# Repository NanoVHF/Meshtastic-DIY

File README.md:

# Meshtastic-DIY

Dear friends. If you have just learned what a Meshtastic-radio network is, if you are interested in the topic, if you already have a radio modem, and you would like to breathe life into it, then …
I have written a large series of 4 articles for the Russian-speaking community. This is more than the usual FAQ. This is a complete guide to action.
At the moment, the articles are written in Russian for a Russian-speaking audience. You can easily translate the article in your google chrome browser into your national language. Perhaps the Google translation will be slightly incorrect, with inaccuracies or errors.
Also, I am considering translating the article into real technical English.

PART 1 : https://habr.com/ru/post/568394/
The article is devoted to the general principles of the Meshtastic-network.

PART 2 : https://habr.com/ru/post/568526/
The article is devoted to branded radio modems with aliexpress stores.

PART 3 : https://habr.com/ru/post/568534/
The article is devoted to the radio amateur design and self-assembly of the radio modem (DIY).

PART 4 : https://habr.com/ru/post/569788/
A detailed step-by-step guide to flashing a radio modem and setting up a local radio network.

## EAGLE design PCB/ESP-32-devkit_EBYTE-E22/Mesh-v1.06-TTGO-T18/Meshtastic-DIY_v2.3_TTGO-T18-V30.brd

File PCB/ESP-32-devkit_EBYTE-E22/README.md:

# PCB

Based on [DIY v.1 shematics](https://github.com/NanoVHF/Meshtastic-DIY/tree/main/Schematics/E-Byte_E22) for using with `ESP32 WROOM-32 DevKit 38 pins` and `EBYTE E22-XXXM30S/E22-XXXM22S` modules.

Design by Denis Gorbunov (https://t.me/deaxx)

## Mesh-v1.01-2LCD-FreePins - Basic
- ESP32 WROOM-32 DevKit 38 pins,
- LORA: EBYTE E22-XXXM30S/E22-XXXM22S (selectable module). LoRa is connected via [an additional adapter board](#ebyte-e22-xxxmxxs-adapter-board),
- GPS,
- LCD (select different screens via jumpers: Vcc/GND or GND/Vcc),
- FR (free pins) - free ESP32 pins are placed along the edges of the board.

## Mesh-v1.02-2LCD - Narrow for placing inside a pipe
- ESP32 WROOM-32 DevKit 38 pins,
- LORA: EBYTE E22-XXXM30S/E22-XXXM22S (selectable module. LoRa module soldered directly to the board,
- GPS,
- LCD (select different screens via jumpers: Vcc/GND or GND/Vcc).

## Mesh-v1.02-2LCD-FreePins - Narrow for placing inside a pipe
- ESP32 WROOM-32 DevKit 38 pins,
- LORA: EBYTE E22-XXXM30S/E22-XXXM22S (selectable module. LoRa module soldered directly to the board,
- GPS,
- LCD (select different screens via jumpers: Vcc/GND or GND/Vcc),
- FR (free pins) - free ESP32 pins are placed along the edges of the board.

## Mesh-v1.03-2LCD-FreePins - Compact wearable
- ESP32 WROOM-32 DevKit 38 pins,
- LORA: EBYTE E22-XXXM30S/E22-XXXM22S (selectable module). LoRa is connected via [an additional adapter board](#ebyte-e22-xxxmxxs-adapter-board),
- GPS,
- LCD (select different screens via jumpers: Vcc/GND or GND/Vcc),
- FR (free pins) - free ESP32 pins are placed along the edges of the board.

## Mesh-v1.04-TTGO-T8 - Compact wearable @ WROOWER T8 Lilygo
- ESP32 *WROOWER T8 Lilygo* 38 pins,
- LORA: EBYTE E22-XXXM30S/E22-XXXM22S (selectable module). LoRa is connected via [an additional adapter board](#ebyte-e22-xxxmxxs-adapter-board),
- GPS,
- LCD (select different screens via jumpers: Vcc/GND or GND/Vcc),
- FR (free pins) - free ESP32 pins are placed along the edges of the board.

## Meshtastic-DIY_v1.05 - Square one
- ESP32 WROOM-32 DevKit 38 pins,
- LORA: EBYTE E22-XXXM30S/E22-XXXM22S (selectable module),
- GPS,
- LCD (select different screens via jumpers: Vcc/GND or GND/Vcc),
- Optional active buzzer.

## Meshtastic-DIY_v1.06 - TTGO T-Energy T18 V3.0 HAT
- *Lilygo TTGO T-Energy T18 V3.0*,
- LORA: EBYTE E22-XXXM30S/E22-XXXM22S (selectable module),
- LCD (select different screens via jumpers: Vcc/GND or GND/Vcc).

## EBYTE E22-xxxMxxS adapter board

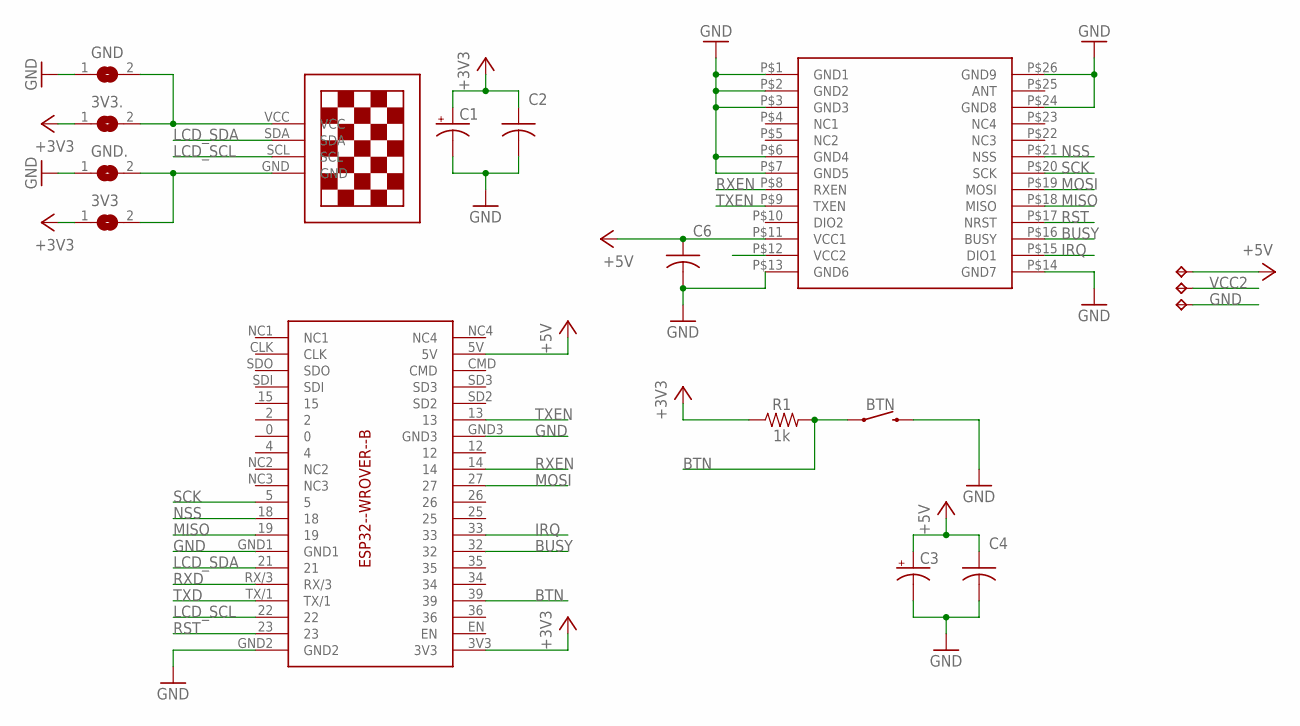
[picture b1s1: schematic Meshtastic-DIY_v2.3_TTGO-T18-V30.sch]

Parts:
3V3, 3V3.: SJ
BTN: MOMENTARY-SWITCH-SPST-SMD-5.2MM; TACTILE_SWITCH_SMD_5.2MM
C1, C3: 100uF; EIA7343
C2, C4, C6: 100nF; C025-024X044
GND, GND.: SJ
R1: 1k; AXIAL-0.1
TP1, TP2, TP3: TPTP14SQ; TP14SQ
U$1: 13"OLED13"OLED; 1.3"OLED
U$2: E22-XXXMXXS
U$4: TTGO-T18_V3

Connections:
+3V3: 3V3.1, 3V3..1, C1.A (+), C2.1, R1.P$1 (1), U$4.3V3
+5V: C3.A (+), C4.1, C6.1, TP1.TP, U$2.P$11 (VCC1), U$4.5V
BTN: BTN.1, R1.P$2 (2), U$4.39
BUSY: U$2.P$16 (BUSY), U$4.32
GND: BTN.3 (2), C1.C (-), C2.2, C3.C (-), C4.2, C6.2, GND.1, GND..1, TP3.TP, U$2.P$1 (GND1), U$2.P$2 (GND2), U$2.P$3 (GND3), U$2.P$6 (GND4), U$2.P$7 (GND5), U$2.P$13 (GND6), U$2.P$14 (GND7), U$2.P$24 (GND8), U$2.P$26 (GND9), U$4.GND1, U$4.GND2, U$4.GND3
IRQ: U$2.P$15 (DIO1), U$4.33
LCD_SCL: U$1.SCL, U$4.22
LCD_SDA: U$1.SDA, U$4.21
MISO: U$2.P$18 (MISO), U$4.19
MOSI: U$2.P$19 (MOSI), U$4.27
unnamed: 3V3.2, GND..2, U$1.GND
unnamed: 3V3..2, GND.2, U$1.VCC
NSS: U$2.P$21 (NSS), U$4.18
RST: U$2.P$17 (NRST), U$4.23
RXD: U$4.RX/3
RXEN: U$2.P$8 (RXEN), U$4.14
SCK: U$2.P$20 (SCK), U$4.5
TXD: U$4.TX/1
TXEN: U$2.P$9 (TXEN), U$4.13
VCC2: TP2.TP, U$2.P$12 (VCC2)

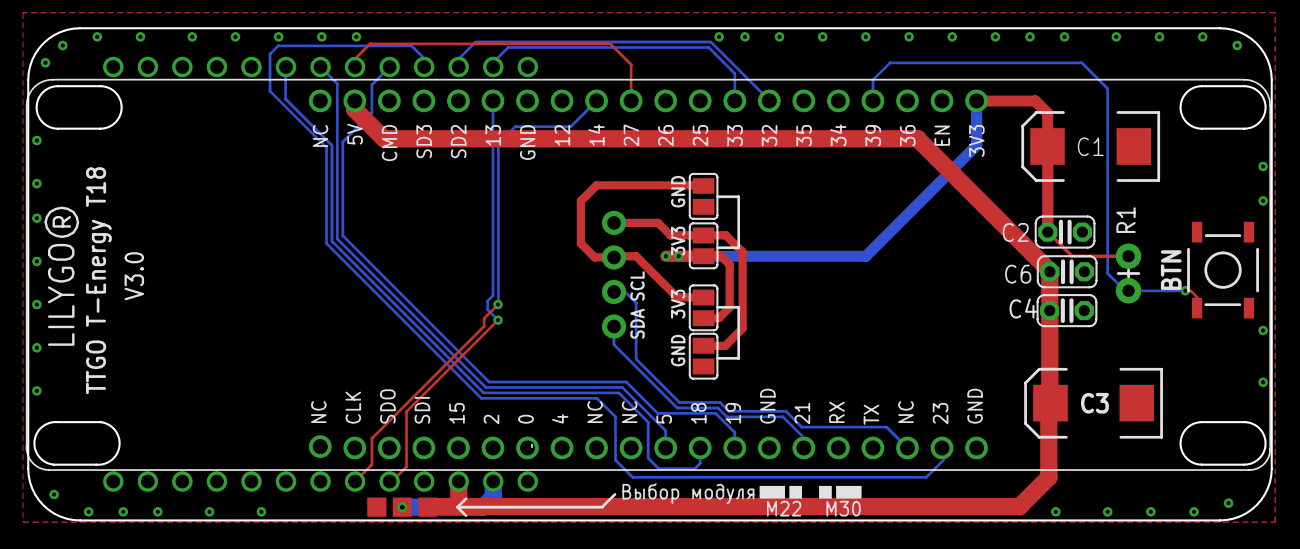
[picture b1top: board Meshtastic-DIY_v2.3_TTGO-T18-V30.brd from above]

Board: 2 copper layers, 91.4 x 36.2 mm, 17 parts (1 on the bottom side), 18 nets.

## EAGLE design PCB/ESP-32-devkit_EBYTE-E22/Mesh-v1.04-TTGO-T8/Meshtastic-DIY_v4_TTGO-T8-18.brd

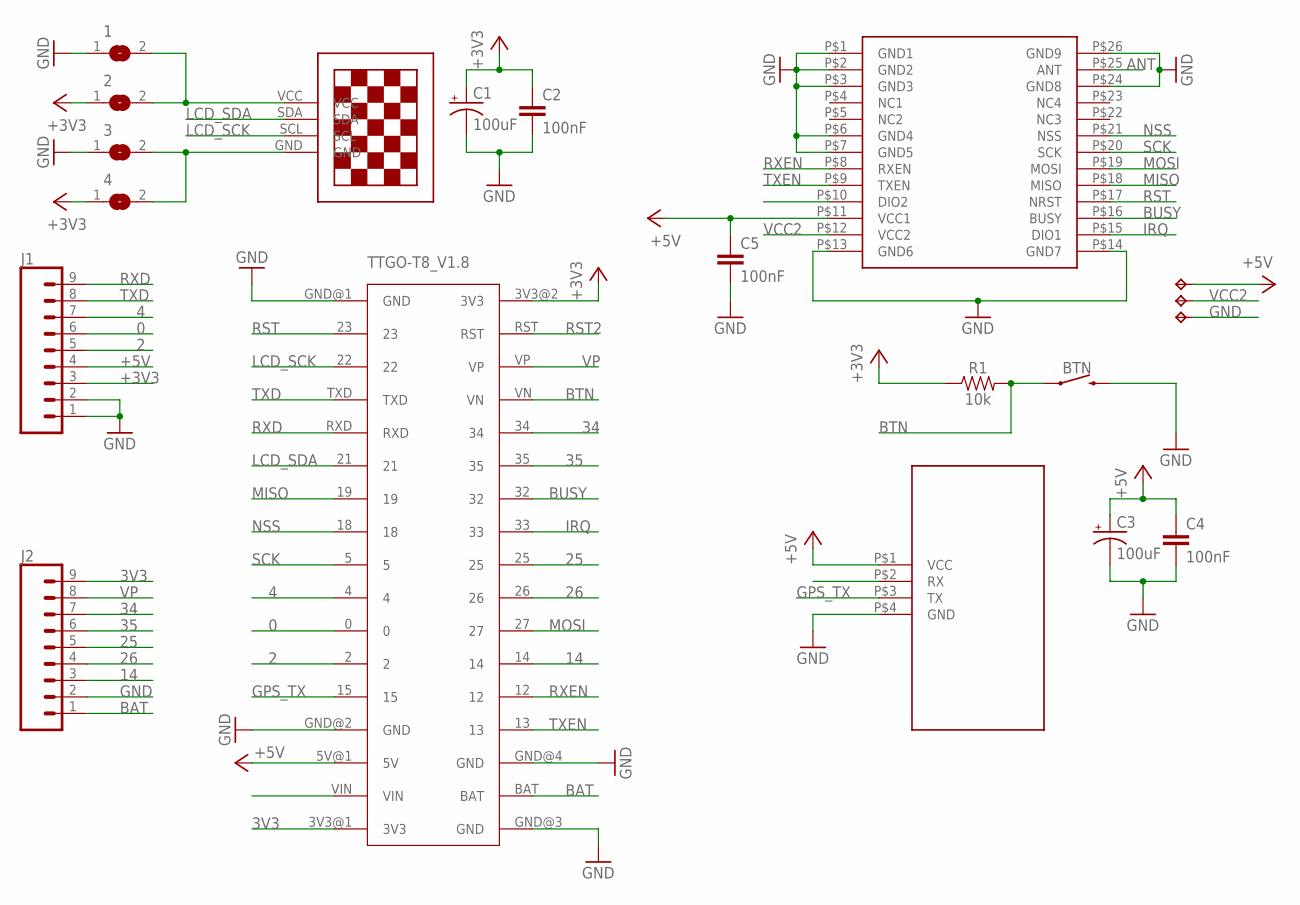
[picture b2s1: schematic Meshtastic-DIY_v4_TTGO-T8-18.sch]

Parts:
1, 2, 3, 4: SJ
BTN: MOMENTARY-SWITCH-SPST-SMD-5.2MM; TACTILE_SWITCH_SMD_5.2MM
C1, C3: 100uF; EIA7343
C2, C4, C5: 100nF; 0805
J1, J2: CONN_09NO_SILK; 1X09_NO_SILK
R1: 10k; 1210
TP1, TP2, TP3: TPTP14SQ; TP14SQ
TTGO-T8_V1.8: TTGO-T8_V18
U$1: 13"OLED13"OLED; 1.3"OLED
U$2: E22-XXXMXXS
U$3: GPS-NEO

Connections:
0: J1.6, TTGO-T8_V1.8.0
2: J1.5, TTGO-T8_V1.8.2
3V3: J2.9, TTGO-T8_V1.8.3V3@1 (3V3)
4: J1.7, TTGO-T8_V1.8.4
14: J2.3, TTGO-T8_V1.8.14
25: J2.5, TTGO-T8_V1.8.25
26: J2.4, TTGO-T8_V1.8.26
34: J2.7, TTGO-T8_V1.8.34
35: J2.6, TTGO-T8_V1.8.35
+3V3: 2.1, 4.1, C1.A (+), C2.1, J1.3, R1.1, TTGO-T8_V1.8.3V3@2 (3V3)
+5V: C3.A (+), C4.1, C5.1, J1.4, TP1.TP, TTGO-T8_V1.8.5V@1 (5V), U$2.P$11 (VCC1), U$3.P$1 (VCC)
ANT: U$2.P$25 (ANT)
BAT: J2.1, TTGO-T8_V1.8.BAT
BTN: BTN.1, R1.2, TTGO-T8_V1.8.VN
BUSY: TTGO-T8_V1.8.32, U$2.P$16 (BUSY)
GND: 1.1, 3.1, BTN.3 (2), C1.C (-), C2.2, C3.C (-), C4.2, C5.2, J1.1, J1.2, J2.2, TP3.TP, TTGO-T8_V1.8.GND@1 (GND), TTGO-T8_V1.8.GND@2 (GND), TTGO-T8_V1.8.GND@3 (GND), TTGO-T8_V1.8.GND@4 (GND), U$2.P$1 (GND1), U$2.P$2 (GND2), U$2.P$3 (GND3), U$2.P$6 (GND4), U$2.P$7 (GND5), U$2.P$13 (GND6), U$2.P$14 (GND7), U$2.P$24 (GND8), U$2.P$26 (GND9), U$3.P$4 (GND)
GPS_TX: TTGO-T8_V1.8.15, U$3.P$3 (TX)
IRQ: TTGO-T8_V1.8.33, U$2.P$15 (DIO1)
LCD_SCK: TTGO-T8_V1.8.22, U$1.SCL
LCD_SDA: TTGO-T8_V1.8.21, U$1.SDA
MISO: TTGO-T8_V1.8.19, U$2.P$18 (MISO)
MOSI: TTGO-T8_V1.8.27, U$2.P$19 (MOSI)
unnamed: 3.2, 4.2, U$1.GND
unnamed: 1.2, 2.2, U$1.VCC
NSS: TTGO-T8_V1.8.18, U$2.P$21 (NSS)
RST: TTGO-T8_V1.8.23, U$2.P$17 (NRST)
RST2: TTGO-T8_V1.8.RST
RXD: J1.9, TTGO-T8_V1.8.RXD
RXEN: TTGO-T8_V1.8.12, U$2.P$8 (RXEN)
SCK: TTGO-T8_V1.8.5, U$2.P$20 (SCK)
TXD: J1.8, TTGO-T8_V1.8.TXD
TXEN: TTGO-T8_V1.8.13, U$2.P$9 (TXEN)
VCC2: TP2.TP, U$2.P$12 (VCC2)
VP: J2.8, TTGO-T8_V1.8.VP

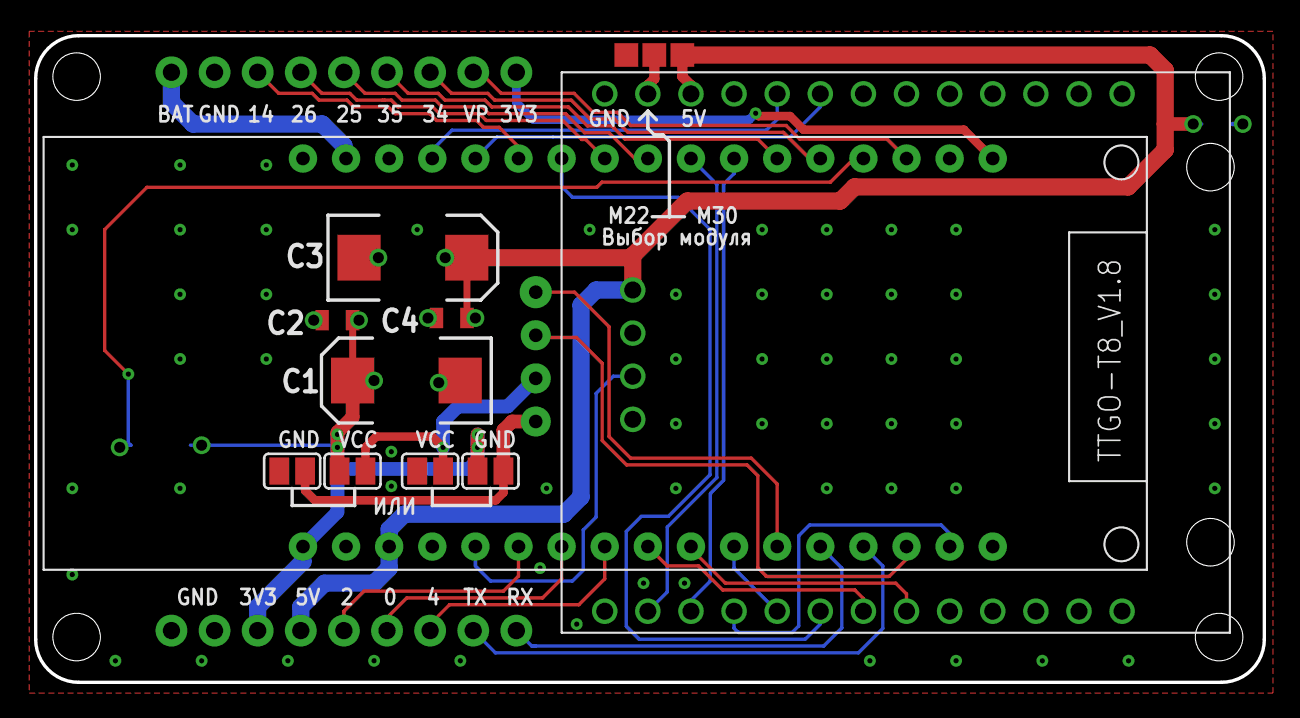
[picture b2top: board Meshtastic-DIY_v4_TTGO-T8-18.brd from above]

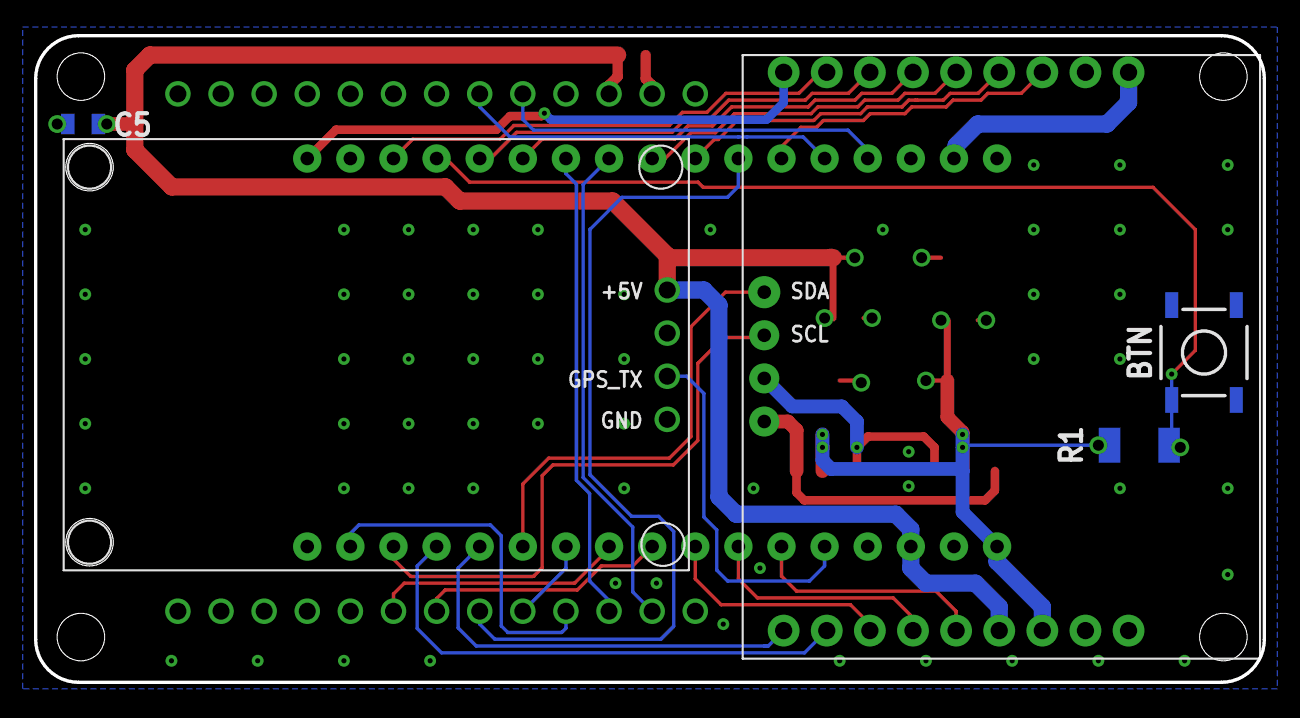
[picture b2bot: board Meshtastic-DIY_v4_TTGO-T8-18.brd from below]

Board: 2 copper layers, 72.4 x 38.1 mm, 20 parts (5 on the bottom side), 32 nets.

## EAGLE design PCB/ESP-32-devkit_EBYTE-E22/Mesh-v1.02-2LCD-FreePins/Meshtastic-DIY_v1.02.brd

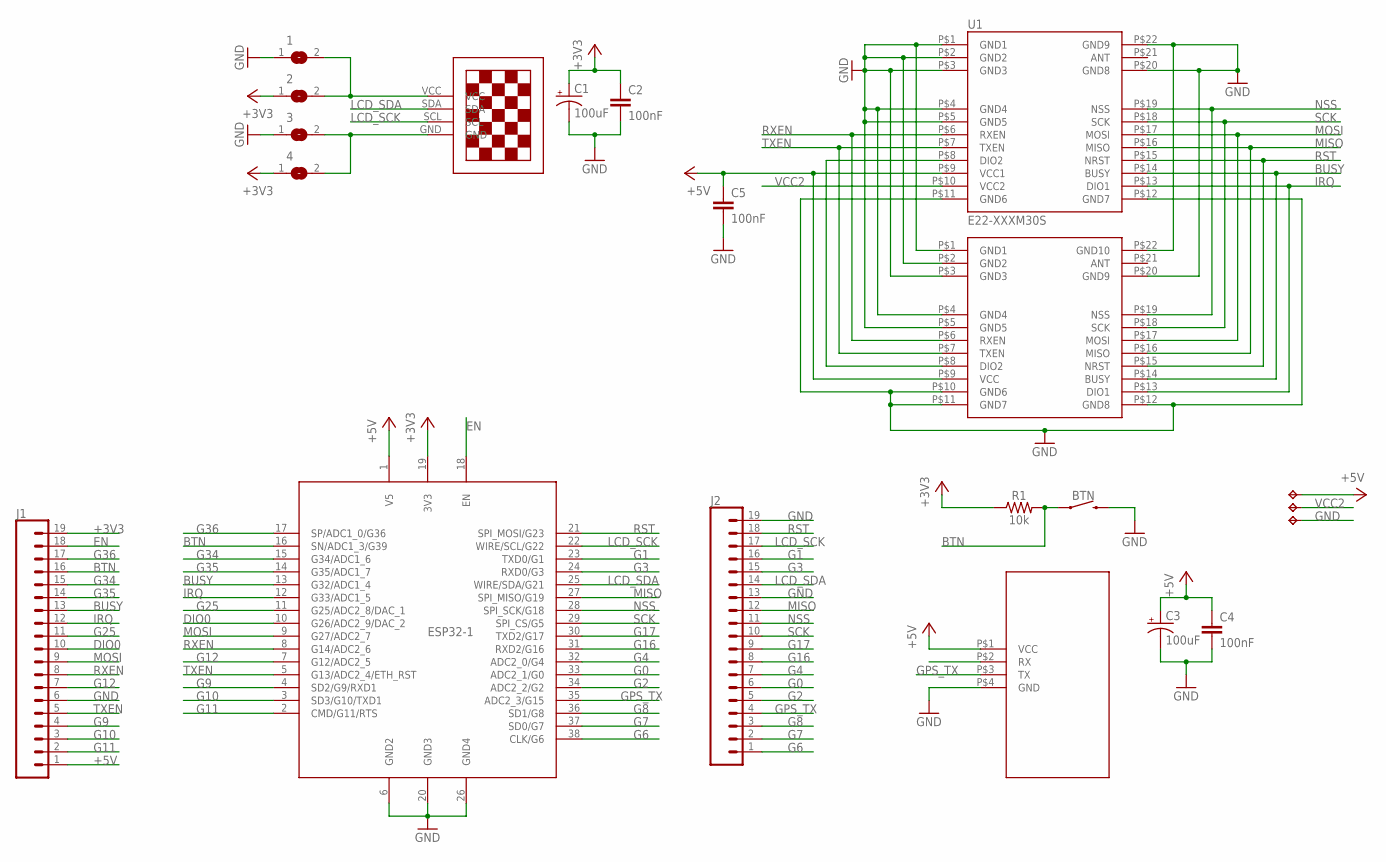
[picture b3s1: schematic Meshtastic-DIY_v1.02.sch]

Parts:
1, 2, 3, 4: SJ
BTN: MOMENTARY-SWITCH-SPST-PTH-6.0MM; TACTILE_SWITCH_PTH_6.0MM
C1, C3: 100uF; EIA7343
C2, C4, C5: 100nF; 0805
ESP32-1: NODEMCU_ESP32_WROOM_32; NODEMCU_ESP32_WROOM_32--38PINS
J1, J2: CONN_191X19_NO_SILK; 1X19_NO_SILK
R1: 10k; 1210
TP1, TP2, TP3: TPTP14SQ; TP14SQ
U1: E22-XXXM30S
U$1: 13"OLED13"OLED; 1.3"OLED
U$2: E22-XXXM22S
U$3: GPS-NEO

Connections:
+3V3: 2.1, 4.1, C1.A (+), C2.1, ESP32-1.19 (3V3), J1.19, R1.1
+5V: C3.A (+), C4.1, C5.1, ESP32-1.1 (V5), J1.1, TP1.TP, U1.P$9 (VCC1), U$2.P$9 (VCC), U$3.P$1 (VCC)
BTN: BTN.1, ESP32-1.16 (SN/ADC1_3/G39), J1.16, R1.2
BUSY: ESP32-1.13 (G32/ADC1_4), J1.13, U1.P$14 (BUSY), U$2.P$14 (BUSY)
DIO0: ESP32-1.10 (G26/ADC2_9/DAC_2), J1.10
EN: ESP32-1.18 (EN), J1.18
G0: ESP32-1.33 (ADC2_1/G0), J2.6
G1: ESP32-1.23 (TXD0/G1), J2.16
G2: ESP32-1.34 (ADC2_2/G2), J2.5
G3: ESP32-1.24 (RXD0/G3), J2.15
G4: ESP32-1.32 (ADC2_0/G4), J2.7
G6: ESP32-1.38 (CLK/G6), J2.1
G7: ESP32-1.37 (SD0/G7), J2.2
G8: ESP32-1.36 (SD1/G8), J2.3
G9: ESP32-1.4 (SD2/G9/RXD1), J1.4
G10: ESP32-1.3 (SD3/G10/TXD1), J1.3
G11: ESP32-1.2 (CMD/G11/RTS), J1.2
G12: ESP32-1.7 (G12/ADC2_5), J1.7
G16: ESP32-1.31 (RXD2/G16), J2.8
G17: ESP32-1.30 (TXD2/G17), J2.9
G25: ESP32-1.11 (G25/ADC2_8/DAC_1), J1.11
G34: ESP32-1.15 (G34/ADC1_6), J1.15
G35: ESP32-1.14 (G35/ADC1_7), J1.14
G36: ESP32-1.17 (SP/ADC1_0/G36), J1.17
GND: 1.1, 3.1, BTN.3 (2), C1.C (-), C2.2, C3.C (-), C4.2, C5.2, ESP32-1.6 (GND2), ESP32-1.20 (GND3), ESP32-1.26 (GND4), J1.6, J2.13, J2.19, TP3.TP, U1.P$1 (GND1), U1.P$2 (GND2), U1.P$3 (GND3), U1.P$4 (GND4), U1.P$5 (GND5), U1.P$11 (GND6), U1.P$12 (GND7), U1.P$20 (GND8), U1.P$22 (GND9), U$2.P$1 (GND1), U$2.P$2 (GND2), U$2.P$3 (GND3), U$2.P$4 (GND4), U$2.P$5 (GND5), U$2.P$10 (GND6), U$2.P$11 (GND7), U$2.P$12 (GND8), U$2.P$20 (GND9), U$2.P$22 (GND10), U$3.P$4 (GND)
GPS_TX: ESP32-1.35 (ADC2_3/G15), J2.4, U$3.P$3 (TX)
IRQ: ESP32-1.12 (G33/ADC1_5), J1.12, U1.P$13 (DIO1), U$2.P$13 (DIO1)
LCD_SCK: ESP32-1.22 (WIRE/SCL/G22), J2.17, U$1.SCL
LCD_SDA: ESP32-1.25 (WIRE/SDA/G21), J2.14, U$1.SDA
MISO: ESP32-1.27 (SPI_MISO/G19), J2.12, U1.P$16 (MISO), U$2.P$16 (MISO)
MOSI: ESP32-1.9 (G27/ADC2_7), J1.9, U1.P$17 (MOSI), U$2.P$17 (MOSI)
unnamed: 3.2, 4.2, U$1.GND
unnamed: 1.2, 2.2, U$1.VCC
unnamed: U1.P$8 (DIO2), U$2.P$8 (DIO2)
NSS: ESP32-1.28 (SPI_SCK/G18), J2.11, U1.P$19 (NSS), U$2.P$19 (NSS)
RST: ESP32-1.21 (SPI_MOSI/G23), J2.18, U1.P$15 (NRST), U$2.P$15 (NRST)
RXEN: ESP32-1.8 (G14/ADC2_6), J1.8, U1.P$6 (RXEN), U$2.P$6 (RXEN)
SCK: ESP32-1.29 (SPI_CS/G5), J2.10, U1.P$18 (SCK), U$2.P$18 (SCK)
TXEN: ESP32-1.5 (G13/ADC2_4/ETH_RST), J1.5, U1.P$7 (TXEN), U$2.P$7 (TXEN)
VCC2: TP2.TP, U1.P$10 (VCC2)

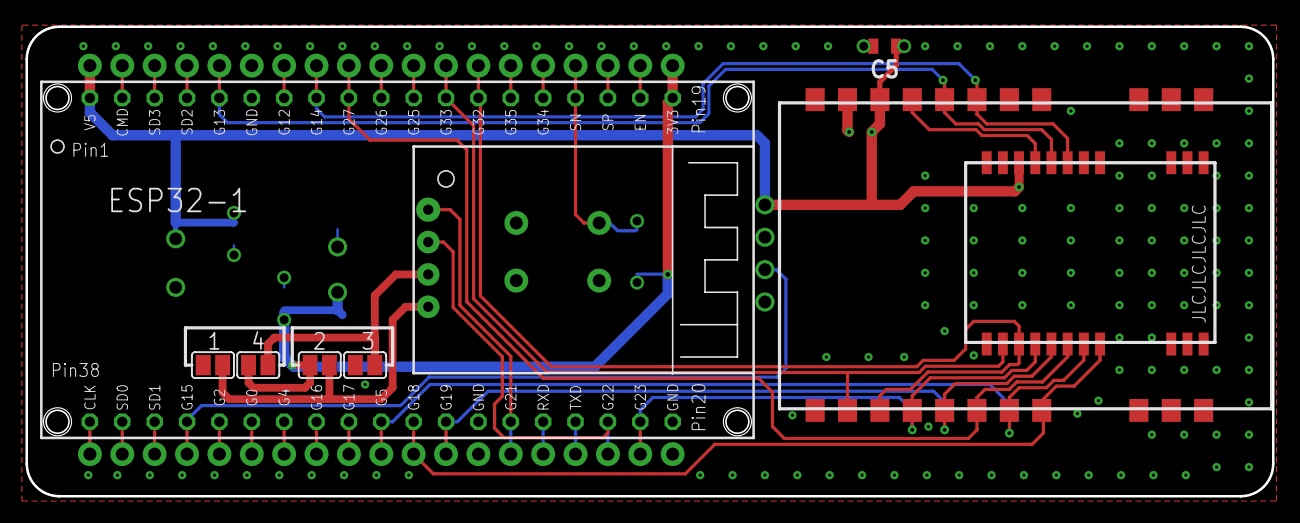
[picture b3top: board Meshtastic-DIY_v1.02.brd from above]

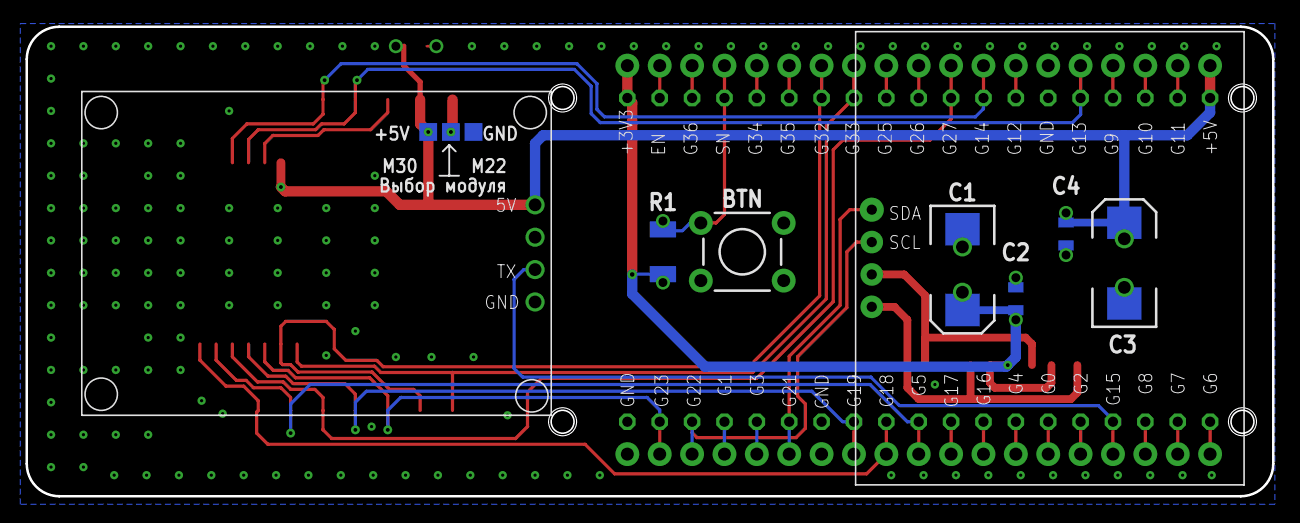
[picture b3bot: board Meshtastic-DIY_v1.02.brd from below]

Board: 2 copper layers, 97.8 x 36.8 mm, 21 parts (11 on the bottom side), 40 nets.

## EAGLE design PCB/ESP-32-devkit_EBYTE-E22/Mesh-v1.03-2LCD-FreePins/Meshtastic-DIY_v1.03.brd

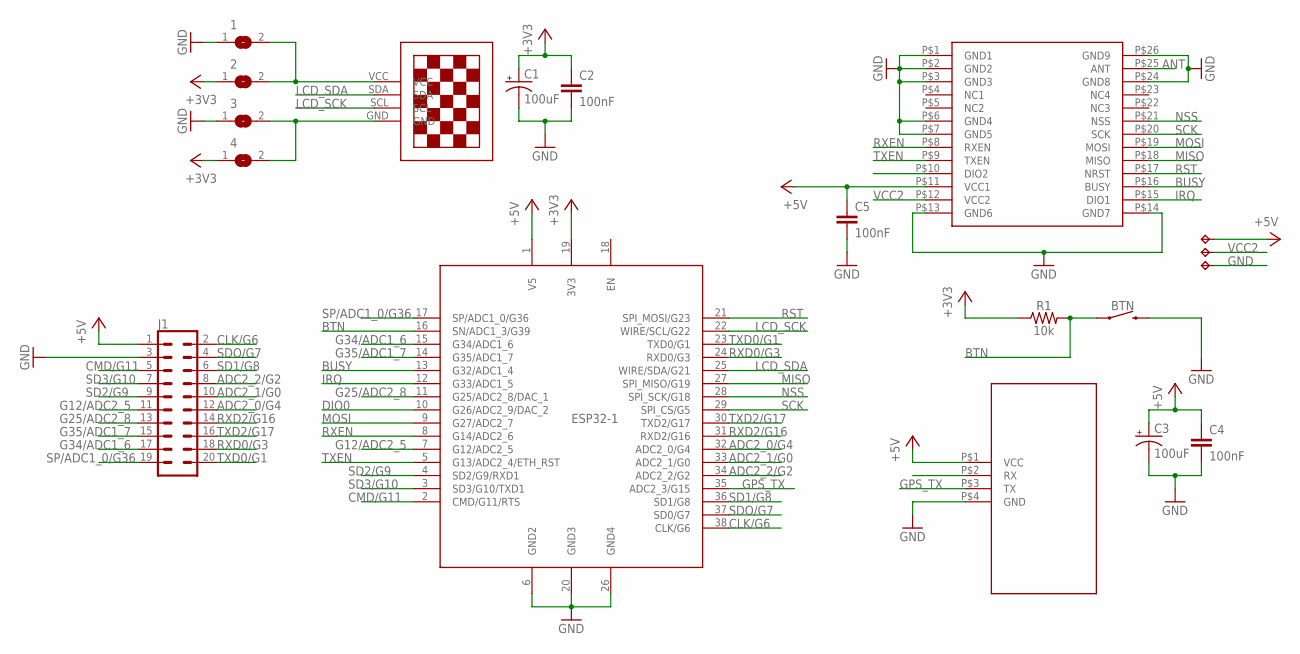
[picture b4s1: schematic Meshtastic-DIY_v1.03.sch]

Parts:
1, 2, 3, 4: SJ
BTN: MOMENTARY-SWITCH-SPST-SMD-5.2MM; TACTILE_SWITCH_SMD_5.2MM
C1, C3: 100uF; EIA7343
C2, C4, C5: 100nF; 0805
ESP32-1: NODEMCU_ESP32_WROOM_32; NODEMCU_ESP32_WROOM_32--38PINS
J1: CONN_10X2NOSILK; 2X10_NOSILK
R1: 10k; 1210
TP1, TP2, TP3: TPTP14SQ; TP14SQ
U$1: 13"OLED13"OLED; 1.3"OLED
U$2: E22-XXXMXXS
U$3: GPS-NEO

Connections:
+3V3: 2.1, 4.1, C1.A (+), C2.1, ESP32-1.19 (3V3), R1.1
+5V: C3.A (+), C4.1, C5.1, ESP32-1.1 (V5), J1.1, TP1.TP, U$2.P$11 (VCC1), U$3.P$1 (VCC)
ADC2_0/G4: ESP32-1.32 (ADC2_0/G4), J1.12
ADC2_1/G0: ESP32-1.33 (ADC2_1/G0), J1.10
ADC2_2/G2: ESP32-1.34 (ADC2_2/G2), J1.8
ANT: U$2.P$25 (ANT)
BTN: BTN.1, ESP32-1.16 (SN/ADC1_3/G39), R1.2
BUSY: ESP32-1.13 (G32/ADC1_4), U$2.P$16 (BUSY)
CLK/G6: ESP32-1.38 (CLK/G6), J1.2
CMD/G11: ESP32-1.2 (CMD/G11/RTS), J1.5
DIO0: ESP32-1.10 (G26/ADC2_9/DAC_2)
G12/ADC2_5: ESP32-1.7 (G12/ADC2_5), J1.11
G25/ADC2_8: ESP32-1.11 (G25/ADC2_8/DAC_1), J1.13
G34/ADC1_6: ESP32-1.15 (G34/ADC1_6), J1.17
G35/ADC1_7: ESP32-1.14 (G35/ADC1_7), J1.15
GND: 1.1, 3.1, BTN.3 (2), C1.C (-), C2.2, C3.C (-), C4.2, C5.2, ESP32-1.6 (GND2), ESP32-1.20 (GND3), ESP32-1.26 (GND4), J1.3, TP3.TP, U$2.P$1 (GND1), U$2.P$2 (GND2), U$2.P$3 (GND3), U$2.P$6 (GND4), U$2.P$7 (GND5), U$2.P$13 (GND6), U$2.P$14 (GND7), U$2.P$24 (GND8), U$2.P$26 (GND9), U$3.P$4 (GND)
GPS_TX: ESP32-1.35 (ADC2_3/G15), U$3.P$3 (TX)
IRQ: ESP32-1.12 (G33/ADC1_5), U$2.P$15 (DIO1)
LCD_SCK: ESP32-1.22 (WIRE/SCL/G22), U$1.SCL
LCD_SDA: ESP32-1.25 (WIRE/SDA/G21), U$1.SDA
MISO: ESP32-1.27 (SPI_MISO/G19), U$2.P$18 (MISO)
MOSI: ESP32-1.9 (G27/ADC2_7), U$2.P$19 (MOSI)
unnamed: 3.2, 4.2, U$1.GND
unnamed: 1.2, 2.2, U$1.VCC
NSS: ESP32-1.28 (SPI_SCK/G18), U$2.P$21 (NSS)
RST: ESP32-1.21 (SPI_MOSI/G23), U$2.P$17 (NRST)
RXD0/G3: ESP32-1.24 (RXD0/G3), J1.18
RXD2/G16: ESP32-1.31 (RXD2/G16), J1.14
RXEN: ESP32-1.8 (G14/ADC2_6), U$2.P$8 (RXEN)
SCK: ESP32-1.29 (SPI_CS/G5), U$2.P$20 (SCK)
SD1/G8: ESP32-1.36 (SD1/G8), J1.6
SD2/G9: ESP32-1.4 (SD2/G9/RXD1), J1.9
SD3/G10: ESP32-1.3 (SD3/G10/TXD1), J1.7
SDO/G7: ESP32-1.37 (SD0/G7), J1.4
SP/ADC1_0/G36: ESP32-1.17 (SP/ADC1_0/G36), J1.19
TXD0/G1: ESP32-1.23 (TXD0/G1), J1.20
TXD2/G17: ESP32-1.30 (TXD2/G17), J1.16
TXEN: ESP32-1.5 (G13/ADC2_4/ETH_RST), U$2.P$9 (TXEN)
VCC2: TP2.TP, U$2.P$12 (VCC2)

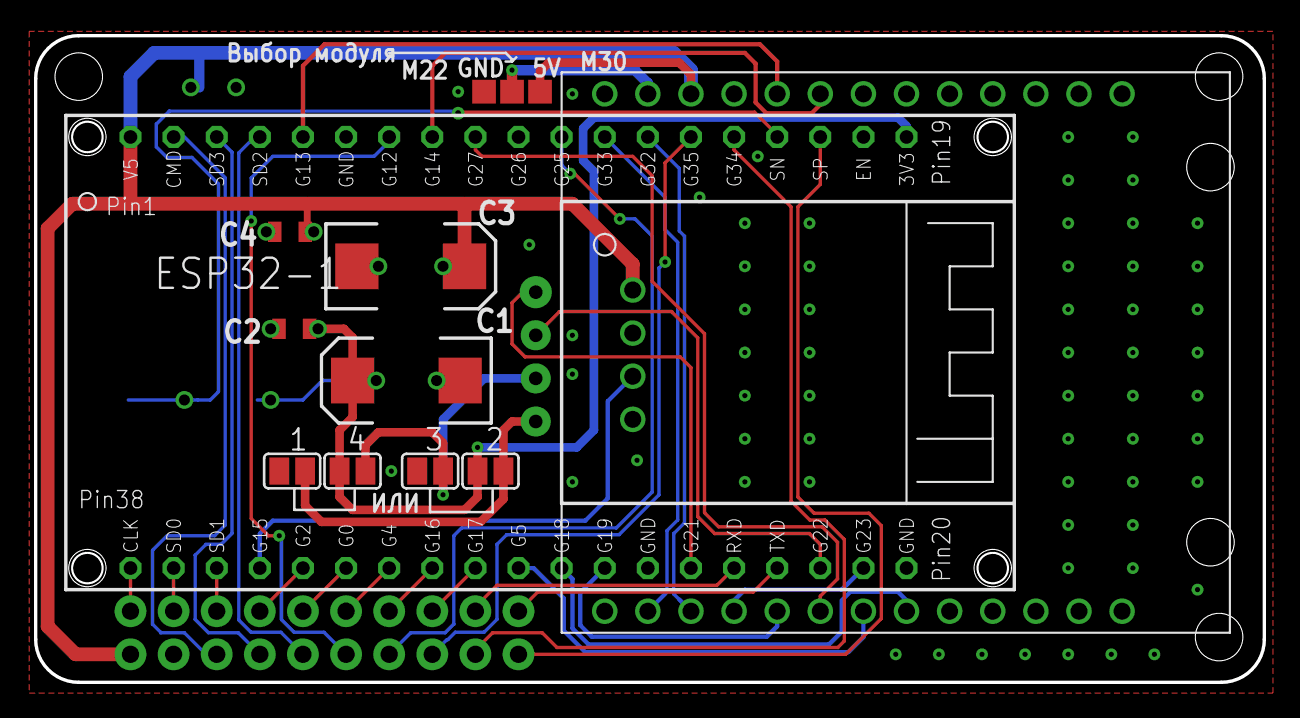
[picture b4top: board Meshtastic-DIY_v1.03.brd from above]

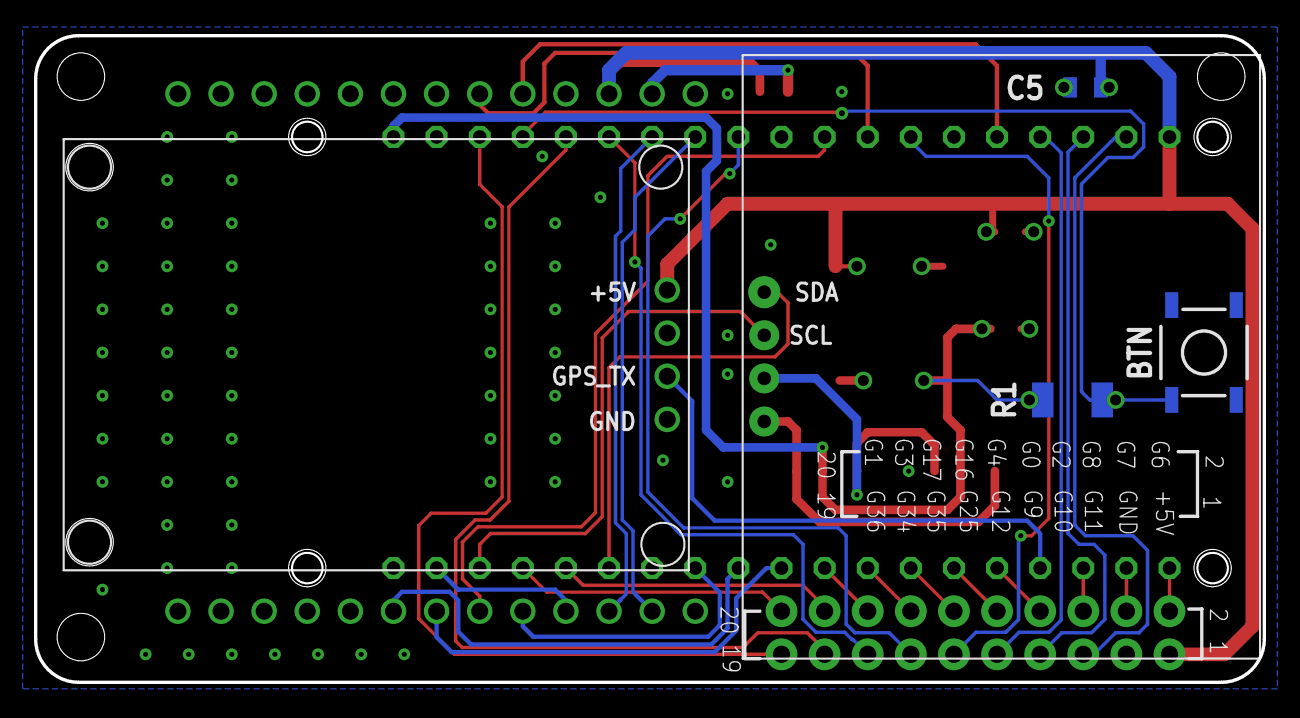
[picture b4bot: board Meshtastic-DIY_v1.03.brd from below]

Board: 2 copper layers, 72.4 x 38.1 mm, 19 parts (5 on the bottom side), 37 nets.

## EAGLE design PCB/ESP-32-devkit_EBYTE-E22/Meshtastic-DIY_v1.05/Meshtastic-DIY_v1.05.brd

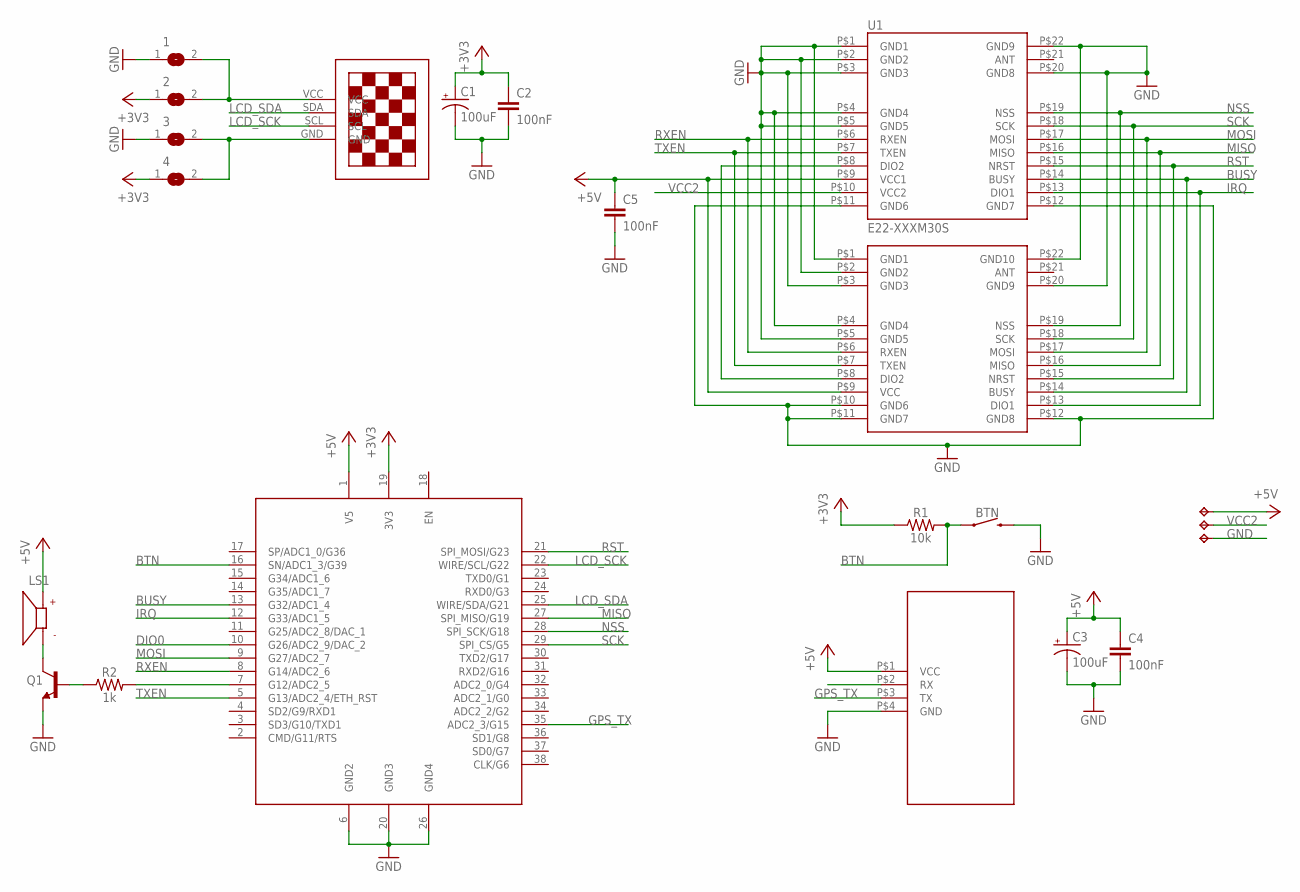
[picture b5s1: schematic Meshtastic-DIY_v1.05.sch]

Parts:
1, 2, 3, 4: SJ
BTN: MOMENTARY-SWITCH-SPST-PTH-6.0MM; TACTILE_SWITCH_PTH_6.0MM
C1, C3: 100uF; CPOL-RADIAL-2.5MM-6.5MM
C2, C4, C5: 100nF; 0805
ESP32-1: NODEMCU_ESP32_WROOM_32; NODEMCU_ESP32_WROOM_32--38PINS
LS1: CMT-0926-86-SMT-TR; XDCR_CMT-0926-86-SMT-TR
Q1: 200mA/40V; TO-92
R1: 10k; 1210
R2: 1k; 1210
TP1, TP2, TP3: TPTP14SQ; TP14SQ
U1: E22-XXXM30S
U$1: 13"OLED13"OLED; 1.3"OLED
U$2: E22-XXXM22S
U$3: GPS-NEO

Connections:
+3V3: 2.1, 4.1, C1.1 (+), C2.1, ESP32-1.19 (3V3), R1.1
+5V: C3.1 (+), C4.1, C5.1, ESP32-1.1 (V5), LS1.P, TP1.TP, U1.P$9 (VCC1), U$2.P$9 (VCC), U$3.P$1 (VCC)
BTN: BTN.1, ESP32-1.16 (SN/ADC1_3/G39), R1.2
BUSY: ESP32-1.13 (G32/ADC1_4), U1.P$14 (BUSY), U$2.P$14 (BUSY)
CMD/G11/RTS: ESP32-1.2 (CMD/G11/RTS)
DIO0: ESP32-1.10 (G26/ADC2_9/DAC_2)
GND: 1.1, 3.1, BTN.3 (2), C1.2 (-), C2.2, C3.2 (-), C4.2, C5.2, ESP32-1.6 (GND2), ESP32-1.20 (GND3), ESP32-1.26 (GND4), Q1.1 (E), TP3.TP, U1.P$1 (GND1), U1.P$2 (GND2), U1.P$3 (GND3), U1.P$4 (GND4), U1.P$5 (GND5), U1.P$11 (GND6), U1.P$12 (GND7), U1.P$20 (GND8), U1.P$22 (GND9), U$2.P$1 (GND1), U$2.P$2 (GND2), U$2.P$3 (GND3), U$2.P$4 (GND4), U$2.P$5 (GND5), U$2.P$10 (GND6), U$2.P$11 (GND7), U$2.P$12 (GND8), U$2.P$20 (GND9), U$2.P$22 (GND10), U$3.P$4 (GND)
GPS_TX: ESP32-1.35 (ADC2_3/G15), U$3.P$3 (TX)
IRQ: ESP32-1.12 (G33/ADC1_5), U1.P$13 (DIO1), U$2.P$13 (DIO1)
LCD_SCK: ESP32-1.22 (WIRE/SCL/G22), U$1.SCL
LCD_SDA: ESP32-1.25 (WIRE/SDA/G21), U$1.SDA
MISO: ESP32-1.27 (SPI_MISO/G19), U1.P$16 (MISO), U$2.P$16 (MISO)
MOSI: ESP32-1.9 (G27/ADC2_7), U1.P$17 (MOSI), U$2.P$17 (MOSI)
unnamed: 1.2, 2.2, U$1.VCC
unnamed: 3.2, 4.2, U$1.GND
unnamed: LS1.N, Q1.3 (C)
unnamed: ESP32-1.7 (G12/ADC2_5), R2.2
unnamed: Q1.2 (B), R2.1
unnamed: U1.P$8 (DIO2), U$2.P$8 (DIO2)
NSS: ESP32-1.28 (SPI_SCK/G18), U1.P$19 (NSS), U$2.P$19 (NSS)
RST: ESP32-1.21 (SPI_MOSI/G23), U1.P$15 (NRST), U$2.P$15 (NRST)
RXEN: ESP32-1.8 (G14/ADC2_6), U1.P$6 (RXEN), U$2.P$6 (RXEN)
SCK: ESP32-1.29 (SPI_CS/G5), U1.P$18 (SCK), U$2.P$18 (SCK)
TXEN: ESP32-1.5 (G13/ADC2_4/ETH_RST), U1.P$7 (TXEN), U$2.P$7 (TXEN)
VCC2: TP2.TP, U1.P$10 (VCC2)

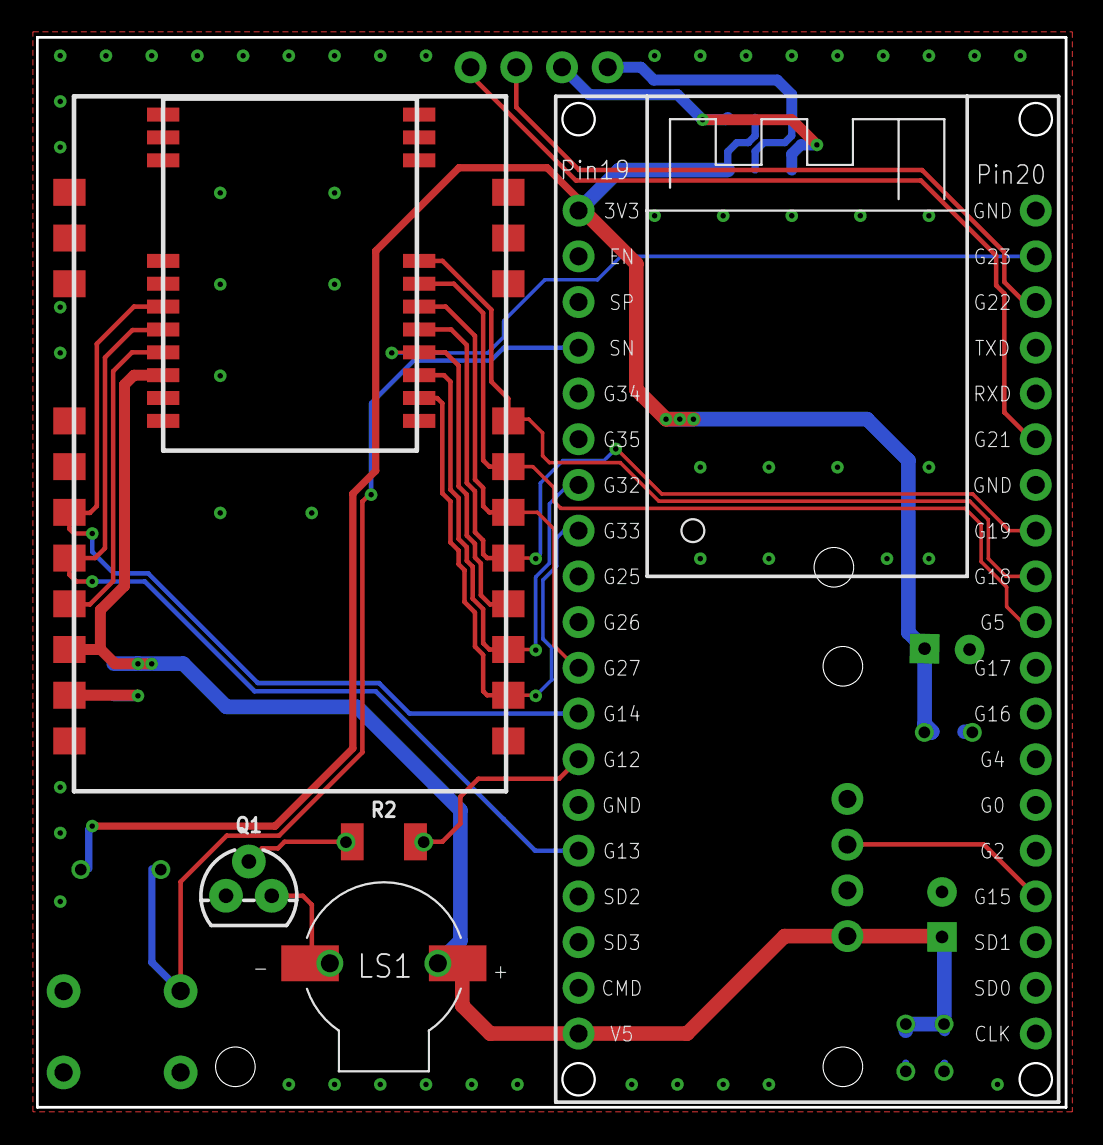
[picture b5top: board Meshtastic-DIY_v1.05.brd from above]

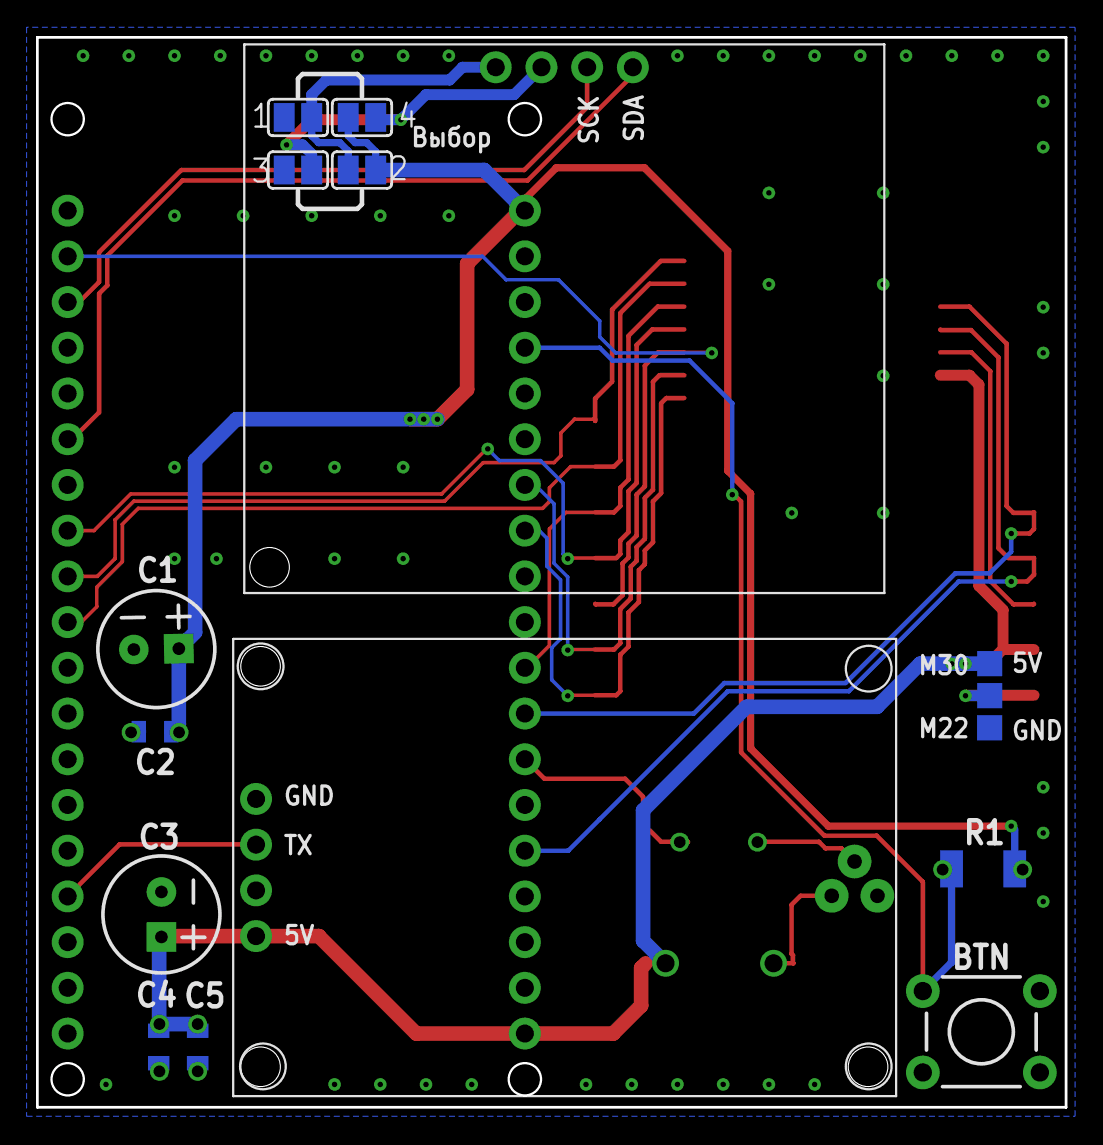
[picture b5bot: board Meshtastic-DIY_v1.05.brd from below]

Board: 2 copper layers, 57.1 x 59.4 mm, 22 parts (16 on the bottom side), 23 nets.

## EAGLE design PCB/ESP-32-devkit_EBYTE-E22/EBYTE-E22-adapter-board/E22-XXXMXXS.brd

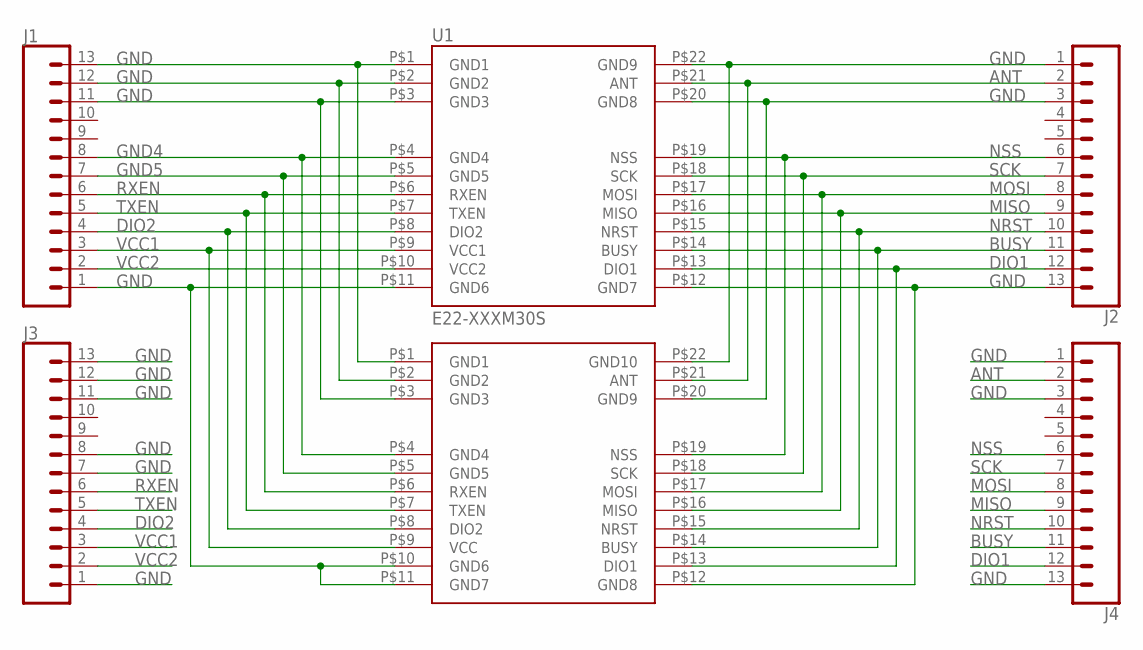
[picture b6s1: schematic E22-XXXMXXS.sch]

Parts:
J1, J2, J3, J4: CONN_13; 1X13
U1: E22-XXXM30S
U$1: E22-XXXM22S

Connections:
ANT: J2.2, J4.2, U1.P$21 (ANT), U$1.P$21 (ANT)
BUSY: J2.11, J4.11, U1.P$14 (BUSY), U$1.P$14 (BUSY)
DIO1: J2.12, J4.12, U1.P$13 (DIO1), U$1.P$13 (DIO1)
DIO2: J1.4, J3.4, U1.P$8 (DIO2), U$1.P$8 (DIO2)
GND: J1.1, J1.11, J1.12, J1.13, J2.1, J2.3, J2.13, J3.1, J3.7, J3.8, J3.11, J3.12, J3.13, J4.1, J4.3, J4.13, U1.P$1 (GND1), U1.P$2 (GND2), U1.P$3 (GND3), U1.P$11 (GND6), U1.P$12 (GND7), U1.P$20 (GND8), U1.P$22 (GND9), U$1.P$1 (GND1), U$1.P$2 (GND2), U$1.P$3 (GND3), U$1.P$10 (GND6), U$1.P$11 (GND7), U$1.P$12 (GND8), U$1.P$20 (GND9), U$1.P$22 (GND10)
GND4: J1.8, U1.P$4 (GND4), U$1.P$4 (GND4)
GND5: J1.7, U1.P$5 (GND5), U$1.P$5 (GND5)
MISO: J2.9, J4.9, U1.P$16 (MISO), U$1.P$16 (MISO)
MOSI: J2.8, J4.8, U1.P$17 (MOSI), U$1.P$17 (MOSI)
NRST: J2.10, J4.10, U1.P$15 (NRST), U$1.P$15 (NRST)
NSS: J2.6, J4.6, U1.P$19 (NSS), U$1.P$19 (NSS)
RXEN: J1.6, J3.6, U1.P$6 (RXEN), U$1.P$6 (RXEN)
SCK: J2.7, J4.7, U1.P$18 (SCK), U$1.P$18 (SCK)
TXEN: J1.5, J3.5, U1.P$7 (TXEN), U$1.P$7 (TXEN)
VCC1: J1.3, J3.3, U1.P$9 (VCC1), U$1.P$9 (VCC)
VCC2: J1.2, J3.2, U1.P$10 (VCC2)

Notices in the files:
parts and their libraries:
SparkFun-Connectors: Licensing: Creative Commons ShareAlike 4.0 International - https://creativecommons.org/licenses/by-sa/4.0
